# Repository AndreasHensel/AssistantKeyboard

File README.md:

# AssistantKeyboard

Based on an Arduino Pro Micro with MEGA32U4 chip this small keyboard can be used for special functions as mic mute, volume etc.
It connects to a PC as an HID device. No PC software needed.

An oled display shows the current function for each key.

TODO: Case

Used material

Pro Micro ATmega32U4
https://www.amazon.de/gp/product/B07J2Q3ZD5/ref=ppx_yo_dt_b_asin_title_o07_s00?ie=UTF8&psc=1
https://de.aliexpress.com/item/32768308647.html?gatewayAdapt=glo2deu&spm=a2g0o.order_list.0.0.21ef5c5f3ADmoW

1,3 Zoll OLED Display I2C SSH1106 Chip 128 x 64
https://www.amazon.de/gp/product/B078J78R45/ref=ppx_yo_dt_b_asin_title_o06_s00?ie=UTF8&psc=1
https://de.aliexpress.com/item/4001145494936.html?gatewayAdapt=glo2deu&spm=a2g0o.order_list.0.0.21ef5c5f3ADmoW

Cherry keys
https://de.aliexpress.com/item/1005002023562636.html?gatewayAdapt=glo2deu&spm=a2g0o.order_list.0.0.21ef5c5f3ADmoW

Key caps
https://de.aliexpress.com/item/1005002996832179.html?gatewayAdapt=glo2deu&spm=a2g0o.order_list.0.0.21ef5c5f3ADmoW

Rotary Encoder
https://de.aliexpress.com/item/1005003084166943.html?gatewayAdapt=glo2deu&spm=a2g0o.order_list.0.0.21ef5c5f3ADmoW

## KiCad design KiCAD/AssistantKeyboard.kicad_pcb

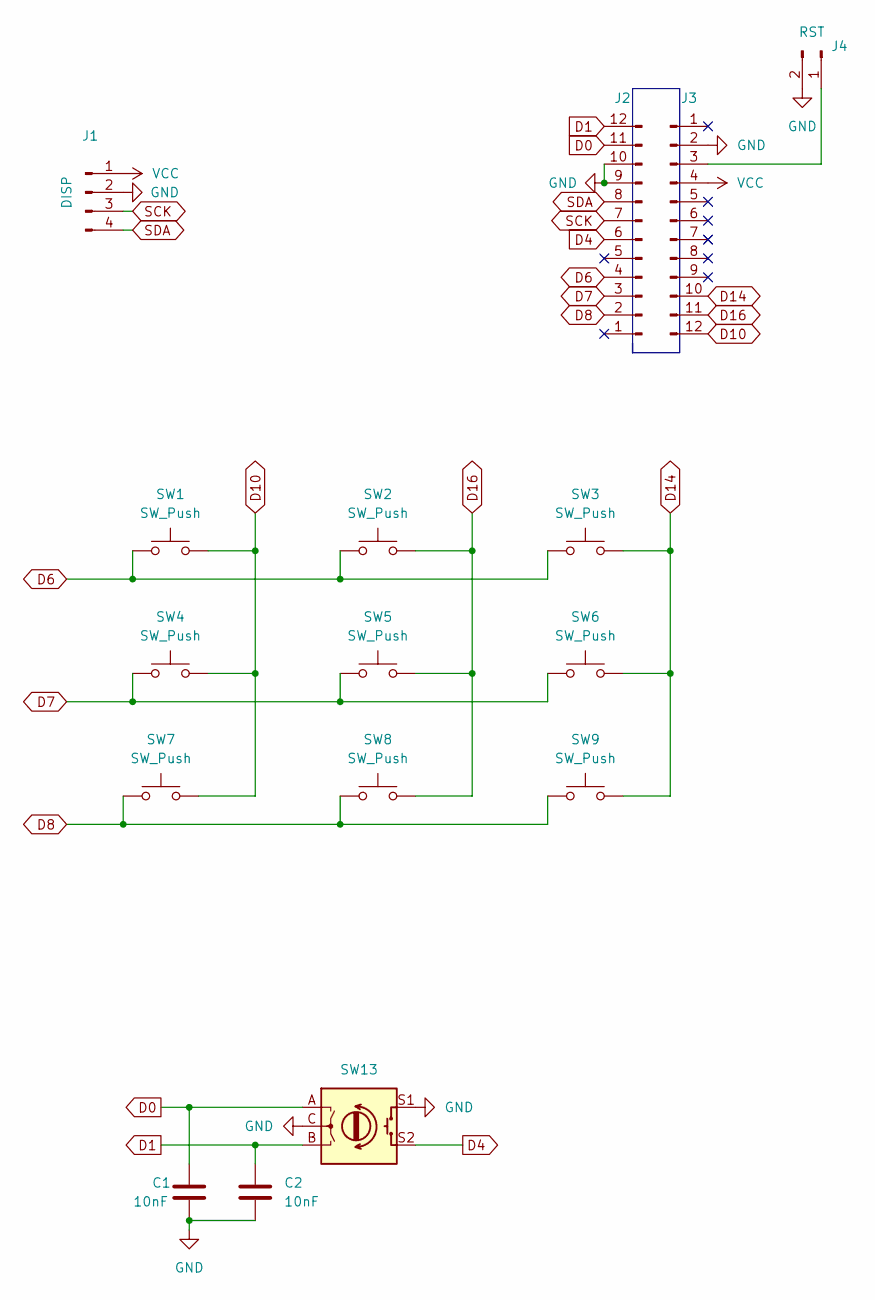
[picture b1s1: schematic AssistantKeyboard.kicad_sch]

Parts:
C1, C2: 10nF; C_0805_2012Metric_Pad1.18x1.45mm_HandSolder
J1: Conn_01x04_Male; PinHeader_1x04_P2.54mm_Vertical
J2, J3: Conn_01x12_Male; PinHeader_1x12_P2.54mm_Vertical
J4: Conn_01x02_Male; PinHeader_1x02_P2.54mm_Vertical
SW1, SW2, SW3, SW4, SW5, SW6, SW7, SW8, SW9: SW_Push; SW_Cherry_MX_1.00u_PCB
SW13: RotaryEncoder_Switch; RotaryEncoder_Alps_EC11E-Switch_Vertical_H20mm

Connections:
D0: C1.1, J2.11, SW13.A
D1: C2.1, J2.12, SW13.B
D4: J2.6, SW13.S2
D6: J2.4, SW1.1, SW2.1, SW3.1
D7: J2.3, SW4.1, SW5.1, SW6.1
D8: J2.2, SW7.1, SW8.1, SW9.1
D10: J3.12, SW1.2, SW4.2, SW7.2
D14: J3.10, SW3.2, SW6.2, SW9.2
D16: J3.11, SW2.2, SW5.2, SW8.2
GND: C1.2, C2.2, J1.2, J2.9, J2.10, J3.2, J4.2, SW13.C, SW13.S1
unnamed: J3.3, J4.1
SCK: J1.3, J2.7
SDA: J1.4, J2.8
VCC: J1.1, J3.4

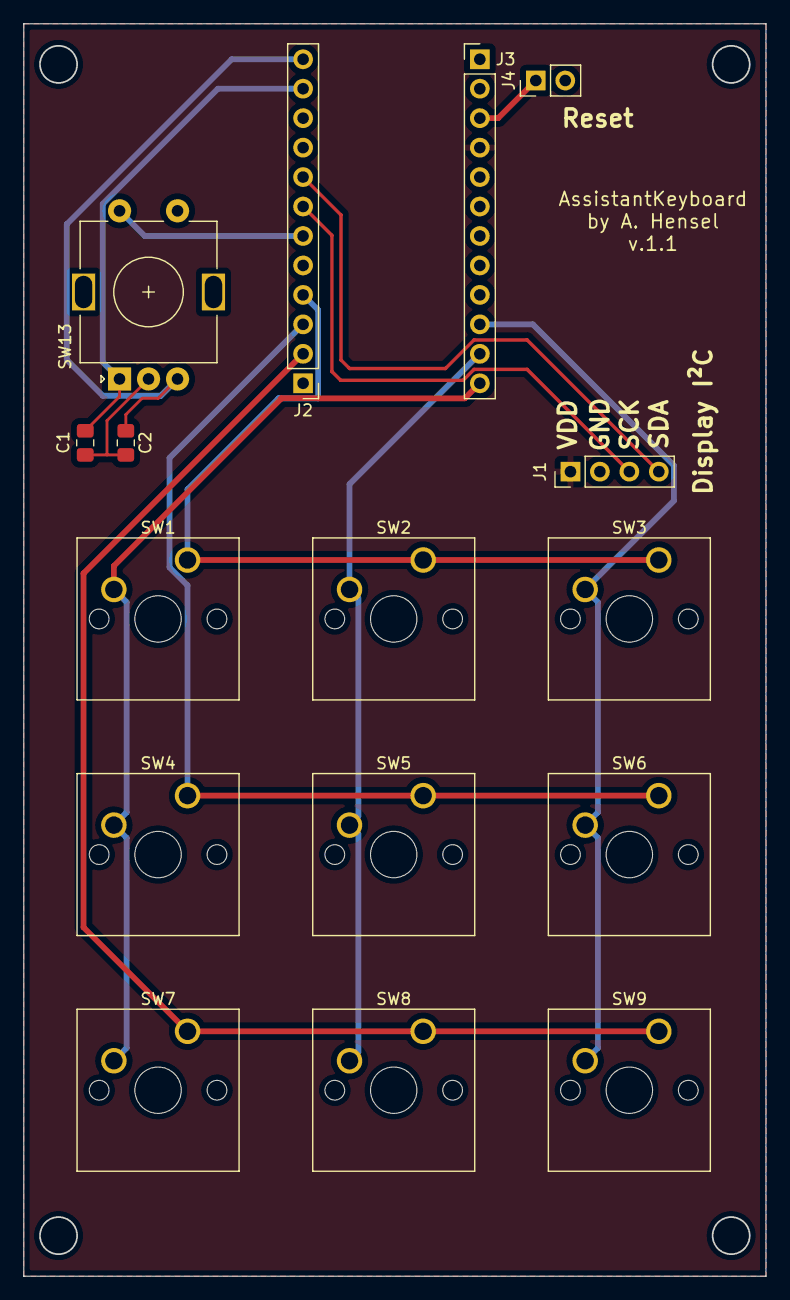
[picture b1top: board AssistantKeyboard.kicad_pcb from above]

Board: 2 copper layers, 64.0 x 108.0 mm, 16 parts (0 on the bottom side), 14 nets.

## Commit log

2022-02-06 KiCAD hinzu
    KiCAD Version 0.1 für Testbestellung und erstes Testgerät
2022-02-06 Es geht los.
2022-02-12 Rotary Encoder function added
2022-02-13 Full functionality
2022-02-13 Begin mechanical design
2022-02-13 Mod Case
2022-02-26 Naming PCB files, code improvements
2022-02-27 Case design
2022-03-11 Minor changes
2022-03-13 V1.0
2022-03-13 BOM in readme.md added
2022-03-20 CAD work
2022-03-27 Case Version 1.0
2022-04-02 Debounce caps
2022-04-02 Documentation, version number on pcb silk screen
